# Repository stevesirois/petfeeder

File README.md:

# petfeeder
DIY PetFeeder (v4) - N.A.P.F. (Not Another Pet Feeder)

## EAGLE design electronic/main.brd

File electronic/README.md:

# PCB Board and electronic components

This board and circuit was design with Autocad Eagle version 9.6.2

The design is quite straight forward with a couple of MOSFET transistor acting as logic level booster since the Arduino Nano 33 IOT operate at 3.3V.

This PCB board can be easily produce by using site as https://jlcpcb.com/ or https://oshpark.com/ . Just follow the instructions on their site to produce the required output files.

## BOM

1 Arduino Nano 33 IoT (Amazon B07VW9TSKD)  
1 Miuzei 20KG Servo Motor High Torque DS3218 (Amazon B07MDM1C3M)  
1 DMS-MG90 SERVOMOTOR RC 5V 9G METAL GEAR (Digikey 1738-1255-ND)  
1 AC/DC WALL MOUNT ADAPTER 5V 15W (Digikey 993-1296-ND)

1 MINI LOAD CELL 100G STRAIGHT BAR (Digikey 1568-1898-ND)  
1 LOAD CELL AMP HX711 (Digikey 1568-1436-ND)  
1 SWITCH PUSH SPDT 0.3A 12V (Digikey 5501MBLKRED)
2 MOSFET N-CH 50V 220MA SOT23-3 (Digikey BSS138CT-ND)  
5 RESHIGHPOWER 0805 10K 1% 1/2W TC (Digikey 118-CMP0805-FX-1002ELFCT-ND)  
1 RES SMD 2K OHM 1% 1/8W 0805 (Digikey CR0805-FX-2001ELFCT-ND)  
1 TERM BLK 2P SIDE ENT 5.08MM PCB (Digikey 609-3936-ND)  
2 CONN HEADER R/A 3POS 2.54MM (Digikey PH1RB-03-UA)
2 CONN HDR 15POS 0.1 TIN PCB (Digikey S7013-ND)

### Hardware

4 SHT MTL SCREW FLAT PHIL #0 1=1 (Digikey SR6001-ND)  
2 M3\*16 bolt (for load cell)  
3 M10 x 500mm threaded rod  
12 M10 x 1.5mm nuts  
12 M10 flat washer  
4 M2 x 10mm screws  
4 M3 x 50mm bolt & nut  
Epoxy glue - 5 min.  

### Note

For those who are not familiar with Autodesk Eagle (a.k.a. Eagle Cad), I generated the job files required to submit your order to JLCPCB in a sub folder.

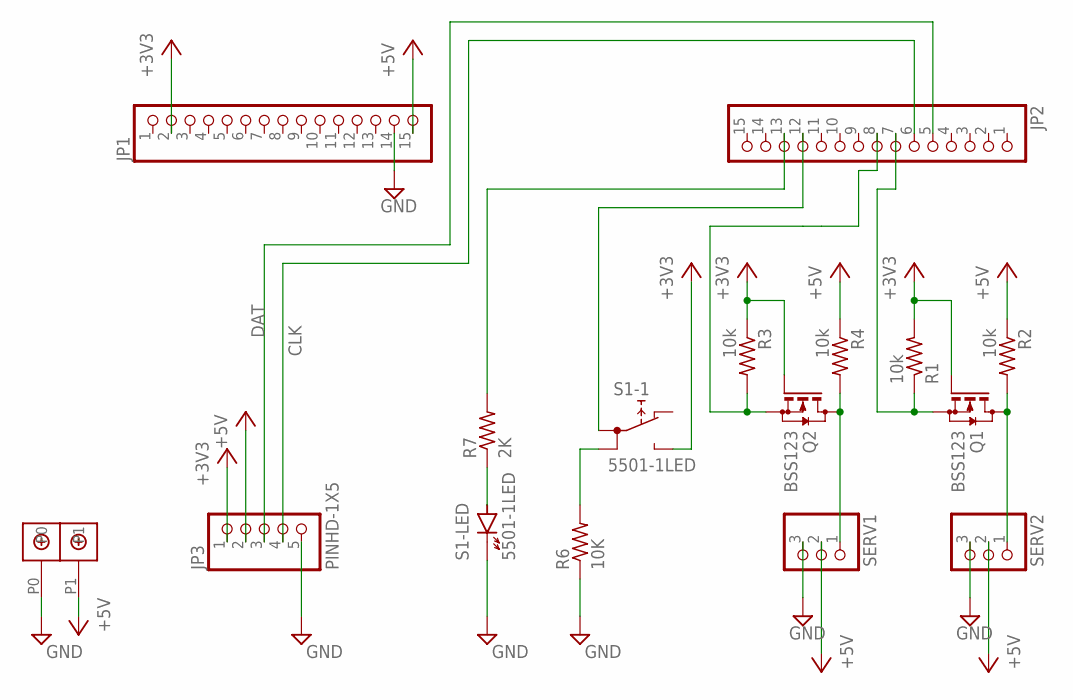
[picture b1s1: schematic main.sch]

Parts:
JP1, JP2: PINHD-1X15; 1X15
JP3: PINHD-1X5; 1X05
Q1, Q2: BSS123; SOT23
R1, R2, R3, R4: 10k; M0805
R6: 10K; M0805
R7: 2K; M0805
S1: 5501-1LED
SERV1, SERV2: PINHD-1X3; 1X03
U$1: DBCONN-1X2

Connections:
+3V3: JP1.2, JP3.1, Q1.1 (G), Q2.1 (G), R1.2, R3.1, S1.NO
+5V: JP1.15, JP3.2, R2.1, R4.1, SERV1.2, SERV2.2, U$1.P1
GND: JP1.14, JP3.5, R6.1, S1.- (K), SERV1.3, SERV2.3, U$1.P0
unnamed: Q2.3 (D), R4.2, SERV1.1
unnamed: Q1.3 (D), R2.2, SERV2.1
unnamed: JP2.7, Q1.2 (S), R1.1
unnamed: JP2.12, S1.1A
unnamed: R7.1, S1.+ (A)
unnamed: JP2.13, R7.2
unnamed: JP2.5, JP3.3
unnamed: JP2.6, JP3.4
unnamed: JP2.8, Q2.2 (S), R3.2
unnamed: R6.2, S1.1B

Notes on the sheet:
DAT
CLK

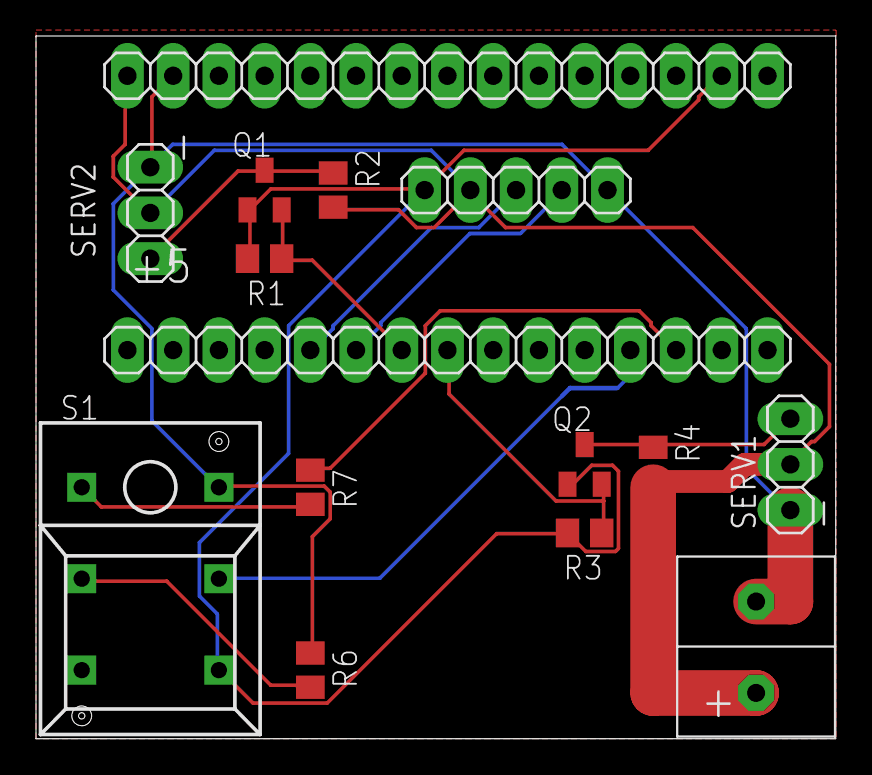
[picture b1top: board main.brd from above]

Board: 2 copper layers, 44.4 x 39.0 mm, 15 parts (0 on the bottom side), 13 nets.

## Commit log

2021-04-05 Initial push
2021-05-02 add ignore and slight ajustment in case of jam
2021-05-03 added inside deflector to funnel
2021-05-03 Updated freecad version
2021-05-03 Added 4 bolt of the food grabber unit
2021-05-03 synthax error
2021-05-09 Proper naming
2021-05-09 added generated files for jlcpcb
2021-05-09 Updated docs
